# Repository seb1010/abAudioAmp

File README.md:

# Overview
  This is a DC coupled class AB amplifier. Additionally power supplies for the positive and negative rail are included on the same board (with the exception of the rectifier diodes and large input filter capacitors). The amplifier has an adjustable gain between 3 and 12 V/V. Everything is constructed from discrete transistors, resistors etc.

## "Voltage Gain Stage"
  * basically just an opamp made with discrete transitors
  * Set up as non-inverting amplifier.
    *  The reasoning behind this was to avoid the impedance of the source effecting the gain. Also using the the non-inverting configuration, the system doesn't have to be stable for unity gain; it only has to be stable for the minimum total gain (3 V/V in this case). However if I tried this with inverting configuration as soon as you unpluged the source the voltage divistion is lost and the system could be unstable.
    * All this said I think it would have been wiser to use an inverting configuration. This would lead to most points in the amplifier seeing essenitally no voltage swing. And I think that could have resulted in overall better performance
 
## Output Stage
  * Common Collector output
  * Adjustable Vbe multiplier to set bias point
  * Not much distortion (when operating by itself (open loop))

The way Vbe varies with temperature adversely effects the circuit. As the temperature of the output transistors increases their collector current increases for the same Vbe; this further increases the temperature. To keep this possitive feedback from turning into thermal runaway I put the Vbe multiplier transistor physically close to the output transitors. This way as the output transistors heat up they heat up this transistor, which reduces the bias voltage and works against the possitive feedback.

This stage has no voltage gain, but it greatly increases the impedance seen by the previous stages. Instead of the 6 ohm speaker it's roughly 6 * 30 * 150 ohms or 30 kOhms.

## Power supply
  * linear regulators for +- 10 volt rails
  This took me a while to get working. I wanted the dominant pole to be formed by the output impedance of the pass transistor and the output capacitor. However this meant that ESR of the output capacitor had to be very small if I wanted any reasonable amount of gain in the feedback path. So I multiple MLCCs in parallel as the output capacitor. I was also careful when laying out the pcb so that the resistance of the traces wouldn't "add" to the ESR as much as possible.

  However with this approch alone I would need very large output capacitors because my difference amplifier itself had a low frequency pole. In order to remedy this I added a capacitor is series with a resitor to the point with the troublesome pole. This had two effects
  1. created a new low frequency pole
  1. pushed the existing pole to a much higher frequency

The first thing may seem problematic, but I could make this pole very low frequency and its phase shift  was "canceled" by a zero before any other poles came into play. This essentially reduced the gain of the error amplifier for important frequencies, This was acceptable because even with this in place I had an open loop gain of 20 V/V or so for these interesting frequencies and that was plenty (open loop the output impedance was already on the order of an ohm)

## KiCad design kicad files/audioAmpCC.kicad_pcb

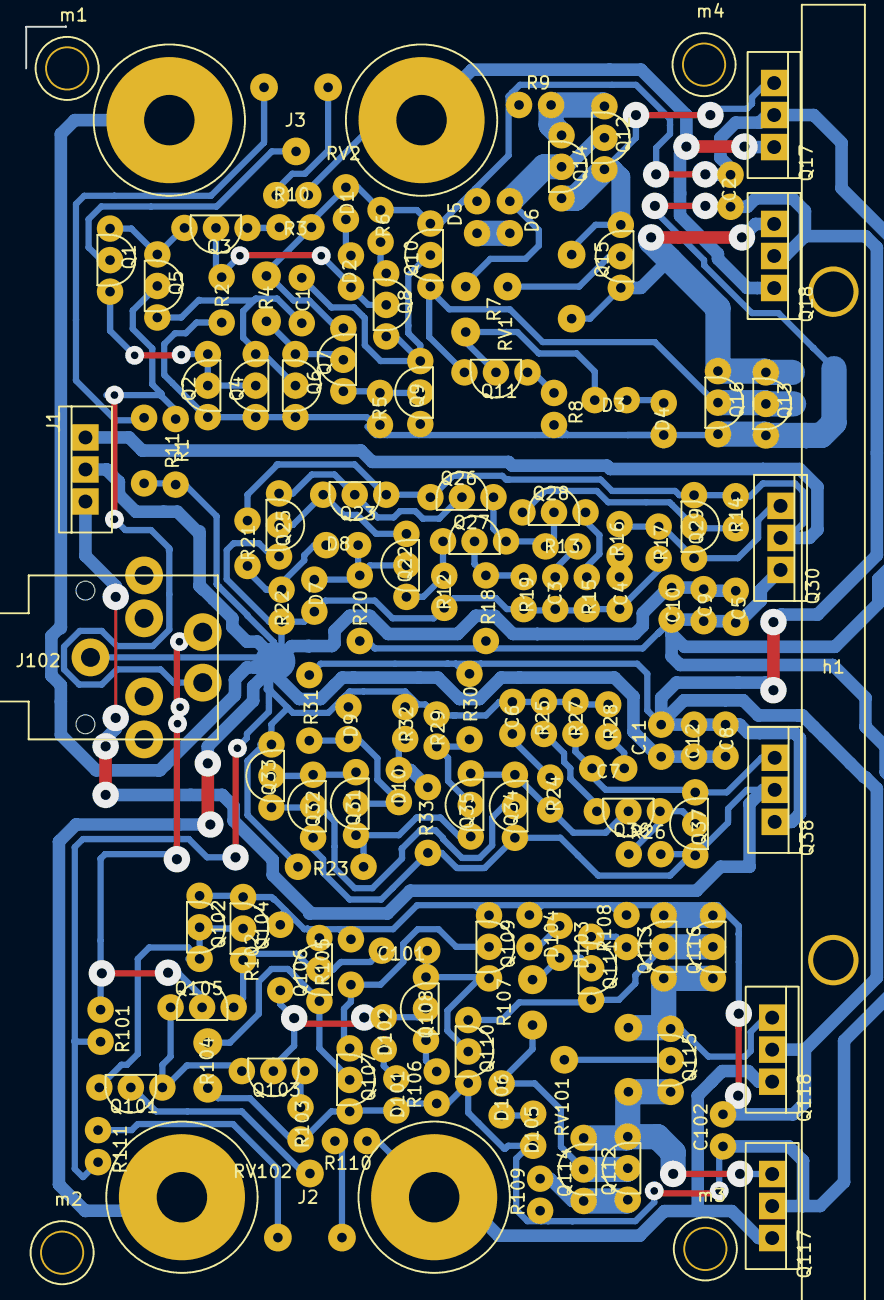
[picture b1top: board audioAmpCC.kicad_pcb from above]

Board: 2 copper layers, 139 parts (0 on the bottom side), 79 nets.

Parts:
C1, C101: C; ResistorJumpTrack
C2, C102: C; ResistorUp
C3, C6: 470n; ResistorUp
C4, C7: 1u; ResistorUp
C5, C9, C11, C12: 20u; ResistorUp
C8, C10: 10u; ResistorUp
D1, D2, D3, D4, D5, D6, D8, D10, D101, D102, D103, D104, D105, D106: D; ResistorUp
D7, D9: D_Zener; ResistorUp
J1: Conn_01x03; to-220sq
J2, J3: Conn_01x02; dual4mmBanana
J102: Conn_01x03; audioJack
Q1, Q3, Q5, Q6, Q8, Q12, Q13, Q14, Q16, Q23, Q25, Q26, Q28, Q29, Q31, Q35, Q101, Q103, Q105, Q106, Q108, Q112, Q113, Q114, Q116: 2N3906; to-92ss
Q2, Q4, Q7, Q9, Q10, Q11, Q15, Q22, Q27, Q32, Q33, Q34, Q36, Q37, Q102, Q104, Q107, Q109, Q110, Q111, Q115: 2N3904; to-92ss
Q17, Q30, Q117: TIP41; to-220sq
Q18, Q38, Q118: TIP42; to-220sq
R1: 1k; ResistorJump5.2mm
R2, R21, R105: 10k; ResistorJumpTrack
R3, R103: 5k6; ResistorUp
R4, R104: R; ResistorJumpTrack
R5: 10k; ResistorUp
R6, R8, R106, R108: 560R; ResistorUp
R7, R107: 2k2; ResistorJumpTrack
R9, R109: 22R; ResistorUp
R10, R110: 330R; ResistorUp
R11: 33R; ResistorJump5.2mm
R12: 22k; ResistorUp
R13, R24: 1k5; ResistorUp
R14, R17, R26, R27, R101: 1k; ResistorUp
R15, R25: 4k7; ResistorUp
R16, R28: 100R; ResistorUp
R18, R30, R33, R102: 10k; ResistorJump5.2mm
R19, R29: 5k1; ResistorUp
R20, R31: 4k7; ResistorJump5.2mm
R22, R32: 1k8; ResistorUp
R23: 22k; ResistorJump5.2mm
R111: 33R; ResistorUp
RV1, RV101: POT; bluePot
RV2, RV102: 100R; bluePot
h1: heatsink; heatsink1
m1, m2, m3, m4: Conn_01x01; m3ScrewHole

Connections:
GND: C3.2, C4.2, C5.2, C6.1, C8.1, C9.2, C10.2, C11.1, C12.1, D7.2, D9.1, J1.2, J2.2, J3.2, J102.2, Q25.3, Q33.3, R1.2, R11.2, R12.2, R15.2, R17.2, R19.2, R22.2, R23.1, R25.1, R27.1, R28.1, R29.1, R32.1, R101.2, R111.2
unnamed: C1.1, Q8.3, Q9.3, Q10.2
unnamed: C1.2, Q4.3, Q5.3, Q6.2
unnamed: C3.1, R13.2
unnamed: C4.1, R16.2
unnamed: C6.2, R24.1
unnamed: C7.1, R28.2
unnamed: C7.2, Q37.3, Q38.1, R27.2
unnamed: C101.1, Q108.3, Q109.3, Q110.2
unnamed: C101.2, Q104.3, Q105.3, Q106.2
unnamed: D1.1, D2.2
unnamed: D2.1, Q3.2, Q8.2, R2.1
unnamed: D3.1, D4.2
unnamed: D3.2, Q11.2, R7.2
unnamed: D5.1, D6.2
unnamed: D6.1, Q12.2, Q14.2, R7.1
unnamed: D7.1, D8.1, Q22.2, R20.2
unnamed: D8.2, R21.2, R22.1
unnamed: D9.2, D10.1, Q31.2, R31.1
unnamed: D10.2, R32.2, R33.1
unnamed: D101.1, D102.2
unnamed: D102.1, Q103.2, Q108.2, R102.1
unnamed: D103.1, D104.2
unnamed: D103.2, Q111.2, R107.2
unnamed: D105.1, D106.2
unnamed: D106.1, Q112.2, Q114.2, R107.1
unnamed: J1.1, Q32.1, Q34.1, Q37.1, Q38.2, R26.2, R33.2
unnamed: J1.3, Q23.1, Q26.1, Q29.1, Q30.2, R14.1, R21.1
unnamed: J2.1, Q117.3, Q118.3, R110.1
unnamed: J3.1, Q17.3, Q18.3, R10.1
unnamed: J102.1, Q105.2, R101.1
unnamed: J102.3, Q5.2, R1.1
unnamed: Q1.1, Q3.3, Q5.1
unnamed: Q1.2, RV2.2
unnamed: Q1.3, Q2.2, Q2.3, Q4.2
unnamed: Q3.1, R3.2
unnamed: Q6.1, Q7.2, R4.2
unnamed: Q7.1, Q9.2, R5.1
unnamed: Q8.1, R6.2
unnamed: Q10.1, Q11.3, Q13.2, Q16.2
unnamed: Q11.1, R8.1
unnamed: Q12.1, Q14.1, R9.2
unnamed: Q12.3, Q14.3, Q15.3, Q17.1, RV1.1
unnamed: Q13.1, Q15.1, Q16.1, Q18.1, RV1.3
unnamed: Q15.2, RV1.2
unnamed: Q22.1, Q27.1, R12.1
unnamed: Q22.3, Q23.3, Q25.2
unnamed: Q23.2, Q25.1, Q26.2
unnamed: Q26.3, Q27.3, Q28.2, R13.1
unnamed: Q27.2, R18.2, R19.1
unnamed: Q28.1, Q29.2, R14.2
unnamed: Q28.3, R15.1
unnamed: Q29.3, Q30.1, R16.1, R17.1
unnamed: Q31.1, Q35.1, R23.2
unnamed: Q31.3, Q32.3, Q33.2
unnamed: Q32.2, Q33.1, Q34.2
unnamed: Q34.3, Q35.3, Q36.2, R24.2
unnamed: Q35.2, R29.2, R30.1
unnamed: Q36.1, Q37.2, R26.1
unnamed: Q36.3, R25.2
unnamed: Q101.1, Q103.3, Q105.1
unnamed: Q101.2, RV102.2
unnamed: Q101.3, Q102.2, Q102.3, Q104.2
unnamed: Q103.1, R103.2
unnamed: Q106.1, Q107.2, R104.2
unnamed: Q107.1, Q109.2, R105.1
unnamed: Q108.1, R106.2
unnamed: Q110.1, Q111.3, Q113.2, Q116.2
unnamed: Q111.1, R108.1
unnamed: Q112.1, Q114.1, R109.2
unnamed: Q112.3, Q114.3, Q115.3, Q117.1, RV101.3
unnamed: Q113.1, Q115.1, Q116.1, Q118.1, RV101.1
unnamed: Q115.2, RV101.2
unnamed: R10.2, RV2.3
unnamed: R11.1, RV2.1
unnamed: R110.2, RV102.1
unnamed: R111.1, RV102.3
VCC: C2.1, C5.1, C9.1, C10.1, C102.1, D1.2, D5.2, D101.2, D105.2, Q7.3, Q10.3, Q17.2, Q30.3, Q107.3, Q110.3, Q117.2, R3.1, R4.1, R6.1, R9.1, R18.1, R20.1, R103.1, R104.1, R106.1, R109.1
VEE: C2.2, C8.2, C11.2, C12.2, C102.2, D4.1, D104.1, Q2.1, Q4.1, Q6.3, Q9.1, Q13.3, Q16.3, Q18.2, Q38.3, Q102.1, Q104.1, Q106.3, Q109.1, Q113.3, Q116.3, Q118.2, R2.2, R5.2, R8.2, R30.2, R31.2, R102.2, R105.2, R108.2

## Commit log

2021-08-04 adding README and kicad
2021-08-04 format readme
2021-09-15 fixed schematic
